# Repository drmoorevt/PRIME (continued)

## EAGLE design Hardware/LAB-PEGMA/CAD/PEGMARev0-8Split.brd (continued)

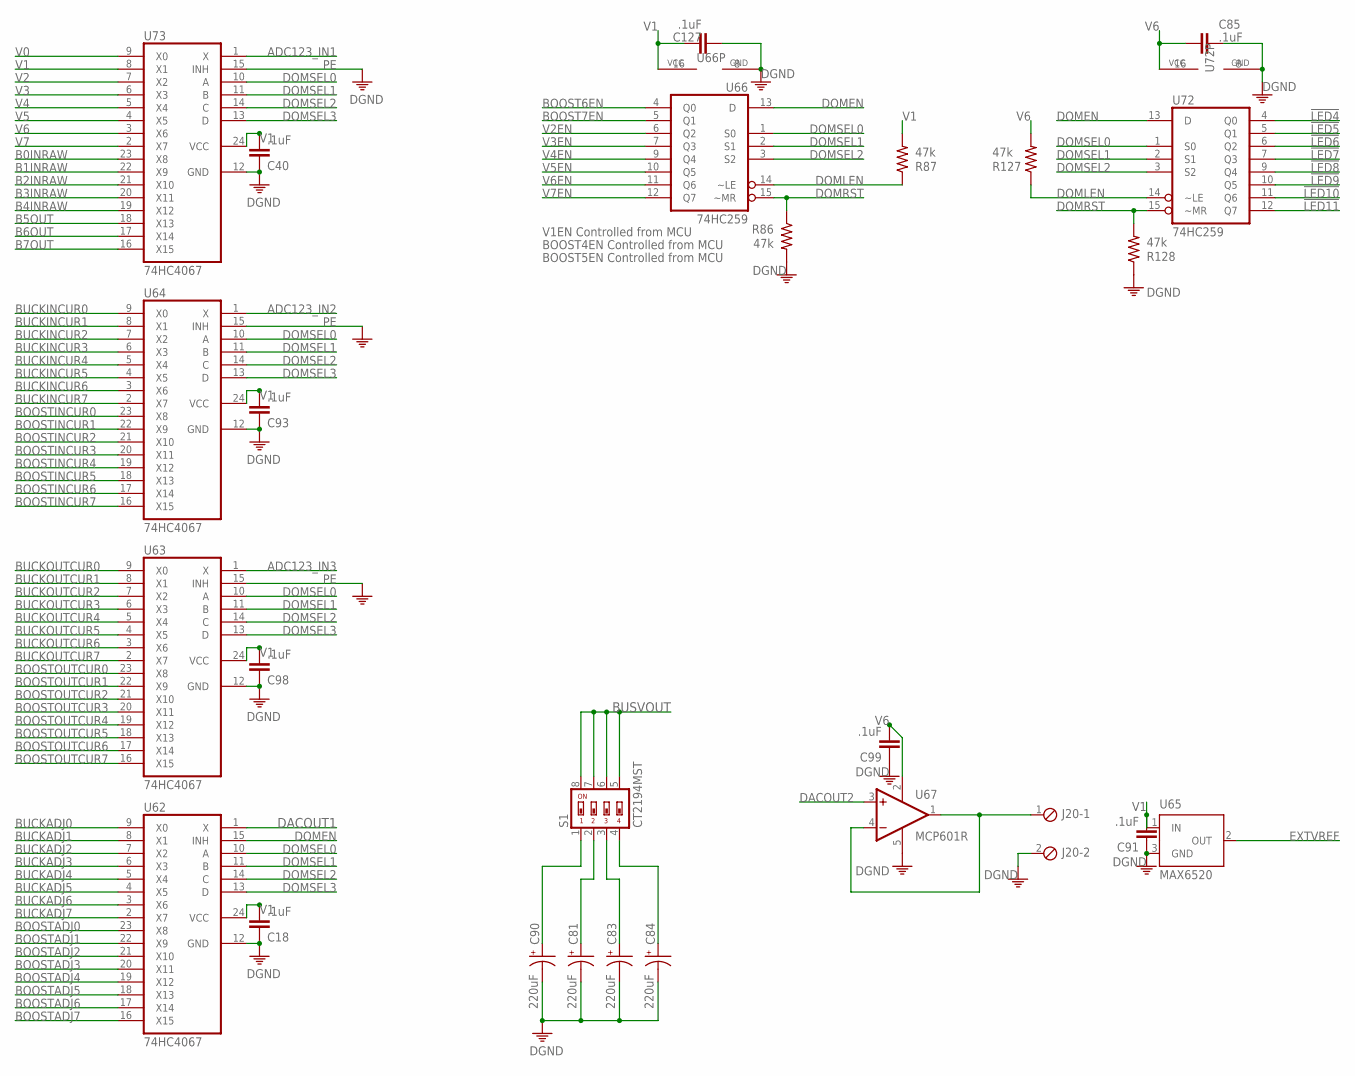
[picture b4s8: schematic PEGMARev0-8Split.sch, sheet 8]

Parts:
C18, C40, C85, C91, C93, C98, C99, C127: .1uF; C0603
C81, C83, C84, C90: 220uF; UD-8X10_NICHICON
J20: MPT2; 2POL254
R86, R87, R127, R128: 47k; R0603
S1: CT2194MST; SMS-004
U62, U63, U64, U73: 74HC4067; SO24W
U65: MAX6520; SOT23
U66, U72: 74HC259; SO16
U67: MCP601R; SOT23-5

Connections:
!LED4: U72.4 (Q0); also elsewhere on the board
!LED5: U72.5 (Q1); also elsewhere on the board
!LED6: U72.6 (Q2); also elsewhere on the board
!LED7: U72.7 (Q3); also elsewhere on the board
!LED8: U72.9 (Q4); also elsewhere on the board
!LED9: U72.10 (Q5); also elsewhere on the board
!LED10: U72.11 (Q6); also elsewhere on the board
!LED11: U72.12 (Q7); also elsewhere on the board
ADC123_IN1: U73.1 (X); also elsewhere on the board
ADC123_IN2: U64.1 (X); also elsewhere on the board
ADC123_IN3: U63.1 (X); also elsewhere on the board
B0INRAW: U73.23 (X8); also elsewhere on the board
B1INRAW: U73.22 (X9); also elsewhere on the board
B2INRAW: U73.21 (X10); also elsewhere on the board
B3INRAW: U73.20 (X11); also elsewhere on the board
B4INRAW: U73.19 (X12); also elsewhere on the board
B5OUT: U73.18 (X13); also elsewhere on the board
B6OUT: U73.17 (X14); also elsewhere on the board
B7OUT: U73.16 (X15); also elsewhere on the board
BOOST6EN: U66.4 (Q0); also elsewhere on the board
BOOST7EN: U66.5 (Q1); also elsewhere on the board
BOOSTADJ0: U62.23 (X8); also elsewhere on the board
BOOSTADJ1: U62.22 (X9); also elsewhere on the board
BOOSTADJ2: U62.21 (X10); also elsewhere on the board
BOOSTADJ3: U62.20 (X11); also elsewhere on the board
BOOSTADJ4: U62.19 (X12); also elsewhere on the board
BOOSTADJ5: U62.18 (X13); also elsewhere on the board
BOOSTADJ6: U62.17 (X14); also elsewhere on the board
BOOSTADJ7: U62.16 (X15); also elsewhere on the board
BOOSTINCUR0: U64.23 (X8); also elsewhere on the board
BOOSTINCUR1: U64.22 (X9); also elsewhere on the board
BOOSTINCUR2: U64.21 (X10); also elsewhere on the board
BOOSTINCUR3: U64.20 (X11); also elsewhere on the board
BOOSTINCUR4: U64.19 (X12); also elsewhere on the board
BOOSTINCUR5: U64.18 (X13); also elsewhere on the board
BOOSTINCUR6: U64.17 (X14); also elsewhere on the board
BOOSTINCUR7: U64.16 (X15); also elsewhere on the board
BOOSTOUTCUR0: U63.23 (X8); also elsewhere on the board
BOOSTOUTCUR1: U63.22 (X9); also elsewhere on the board
BOOSTOUTCUR2: U63.21 (X10); also elsewhere on the board
BOOSTOUTCUR3: U63.20 (X11); also elsewhere on the board
BOOSTOUTCUR4: U63.19 (X12); also elsewhere on the board
BOOSTOUTCUR5: U63.18 (X13); also elsewhere on the board
BOOSTOUTCUR6: U63.17 (X14); also elsewhere on the board
BOOSTOUTCUR7: U63.16 (X15); also elsewhere on the board
BUCKADJ0: U62.9 (X0); also elsewhere on the board
BUCKADJ1: U62.8 (X1); also elsewhere on the board
BUCKADJ2: U62.7 (X2); also elsewhere on the board
BUCKADJ3: U62.6 (X3); also elsewhere on the board
BUCKADJ4: U62.5 (X4); also elsewhere on the board
BUCKADJ5: U62.4 (X5); also elsewhere on the board
BUCKADJ6: U62.3 (X6); also elsewhere on the board
BUCKADJ7: U62.2 (X7); also elsewhere on the board
BUCKINCUR0: U64.9 (X0); also elsewhere on the board
BUCKINCUR1: U64.8 (X1); also elsewhere on the board
BUCKINCUR2: U64.7 (X2); also elsewhere on the board
BUCKINCUR3: U64.6 (X3); also elsewhere on the board
BUCKINCUR4: U64.5 (X4); also elsewhere on the board
BUCKINCUR5: U64.4 (X5); also elsewhere on the board
BUCKINCUR6: U64.3 (X6); also elsewhere on the board
BUCKINCUR7: U64.2 (X7); also elsewhere on the board
BUCKOUTCUR0: U63.9 (X0); also elsewhere on the board
BUCKOUTCUR1: U63.8 (X1); also elsewhere on the board
BUCKOUTCUR2: U63.7 (X2); also elsewhere on the board
BUCKOUTCUR3: U63.6 (X3); also elsewhere on the board
BUCKOUTCUR4: U63.5 (X4); also elsewhere on the board
BUCKOUTCUR5: U63.4 (X5); also elsewhere on the board
BUCKOUTCUR6: U63.3 (X6); also elsewhere on the board
BUCKOUTCUR7: U63.2 (X7); also elsewhere on the board
BUSVOUT: S1.5, S1.6, S1.7, S1.8; also elsewhere on the board
DACOUT1: U62.1 (X); also elsewhere on the board
DACOUT2: U67.3 (+IN); also elsewhere on the board
DOMEN: U62.15 (INH), U66.13 (D), U72.13 (D); also elsewhere on the board
DOMLEN: R87.1, R127.1, U66.14 (~LE), U72.14 (~LE); also elsewhere on the board
DOMRST: R86.1, R128.2, U66.15 (~MR), U72.15 (~MR); also elsewhere on the board
DOMSEL0: U62.10 (A), U63.10 (A), U64.10 (A), U66.1 (S0), U72.1 (S0), U73.10 (A); also elsewhere on the board
DOMSEL1: U62.11 (B), U63.11 (B), U64.11 (B), U66.2 (S1), U72.2 (S1), U73.11 (B); also elsewhere on the board
DOMSEL2: U62.14 (C), U63.14 (C), U64.14 (C), U66.3 (S2), U72.3 (S2), U73.14 (C); also elsewhere on the board
DOMSEL3: U62.13 (D), U63.13 (D), U64.13 (D), U73.13 (D); also elsewhere on the board
EXTVREF: U65.2 (OUT); also elsewhere on the board
unnamed: C83.+, S1.3
unnamed: C90.+, S1.1
unnamed: C81.+, S1.2
unnamed: C84.+, S1.4
unnamed: J20.1, U67.1 (OUT), U67.4 (-IN)
PE: C18.1, C40.1, C81.-, C83.-, C84.-, C85.1, C90.-, C91.1, C93.1, C98.1, C99.1, C127.1, J20.2, R86.2, R128.1, U62.12 (GND), U63.12 (GND), U63.15 (INH), U64.12 (GND), U64.15 (INH), U65.3 (GND), U66.8 (GND), U67.5 (V-), U72.8 (GND), U73.12 (GND), U73.15 (INH); also elsewhere on the board
V0: U73.9 (X0); also elsewhere on the board
V1: C18.2, C40.2, C91.2, C93.2, C98.2, C127.2, R87.2, U62.24 (VCC), U63.24 (VCC), U64.24 (VCC), U65.1 (IN), U66.16 (VCC), U73.8 (X1), U73.24 (VCC); also elsewhere on the board
V2: U73.7 (X2); also elsewhere on the board
V2EN: U66.6 (Q2); also elsewhere on the board
V3: U73.6 (X3); also elsewhere on the board
V3EN: U66.7 (Q3); also elsewhere on the board
V4: U73.5 (X4); also elsewhere on the board
V4EN: U66.9 (Q4); also elsewhere on the board
V5: U73.4 (X5); also elsewhere on the board
V5EN: U66.10 (Q5); also elsewhere on the board
V6: C85.2, C99.2, R127.2, U67.2 (V+), U72.16 (VCC), U73.3 (X6); also elsewhere on the board
V6EN: U66.11 (Q6); also elsewhere on the board
V7: U73.2 (X7); also elsewhere on the board
V7EN: U66.12 (Q7); also elsewhere on the board

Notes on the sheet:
V1EN Controlled from MCU
BOOST4EN Controlled from MCU
BOOST5EN Controlled from MCU

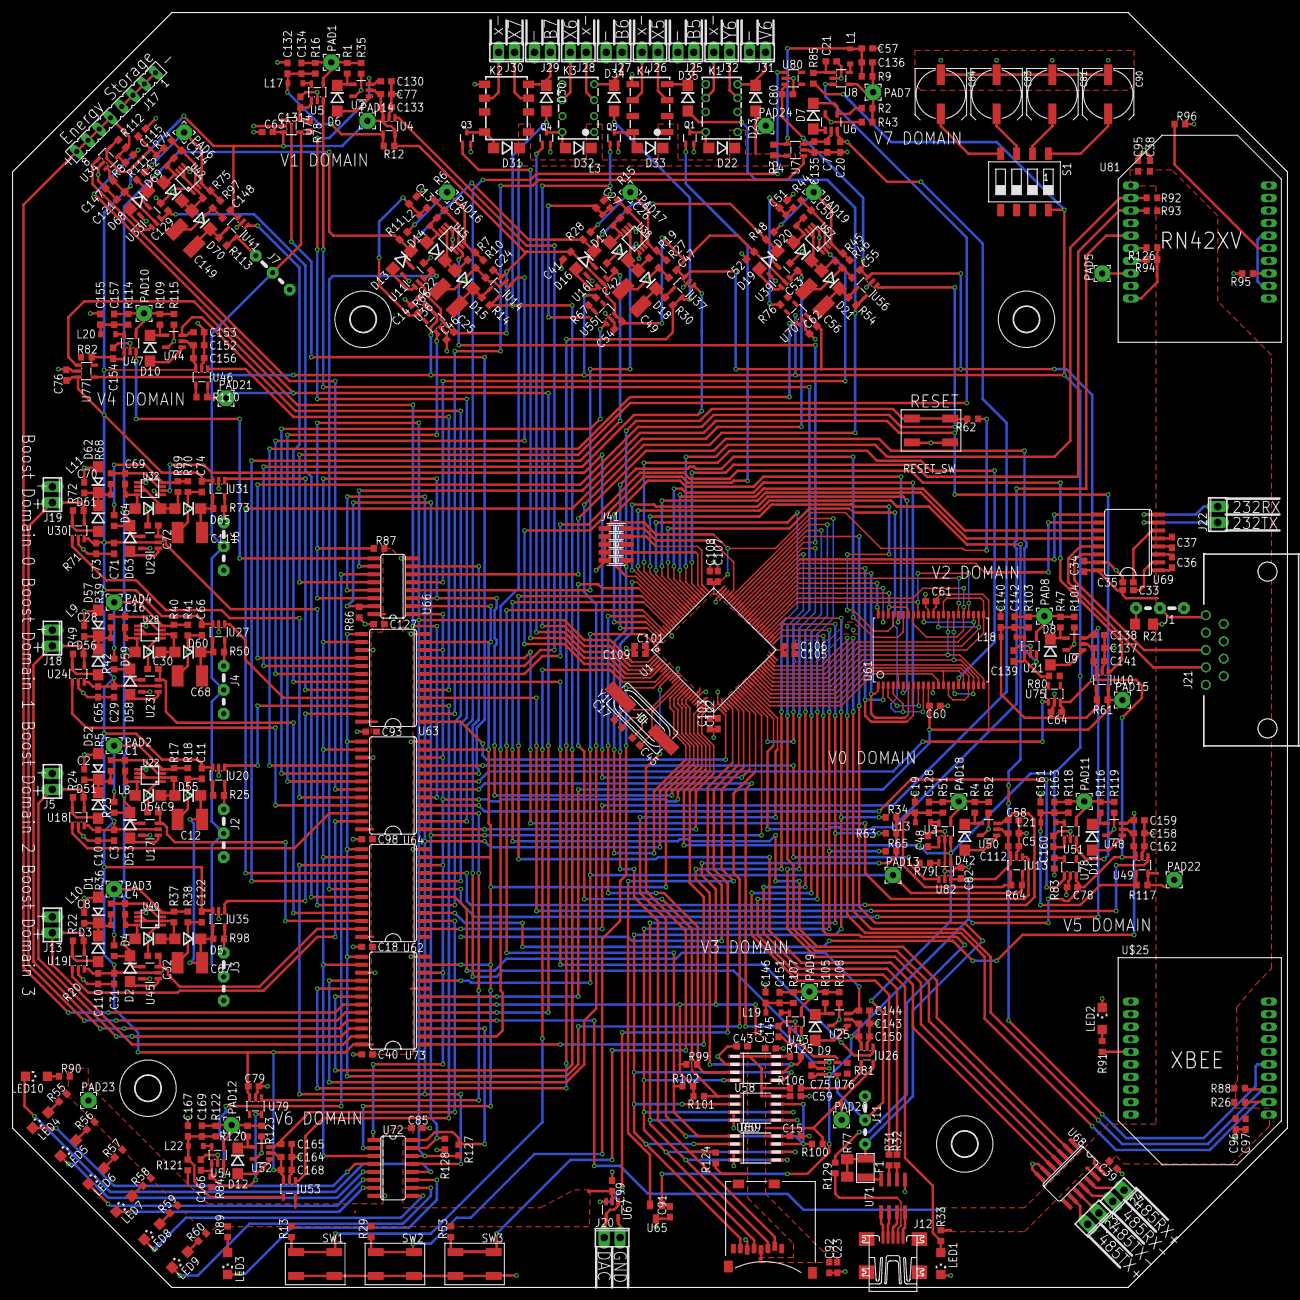
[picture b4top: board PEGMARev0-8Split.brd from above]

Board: 2 copper layers, 203.2 x 203.2 mm, 508 parts (0 on the bottom side), 341 nets.

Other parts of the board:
U$1, U$2, U$3, U$4: 4,1

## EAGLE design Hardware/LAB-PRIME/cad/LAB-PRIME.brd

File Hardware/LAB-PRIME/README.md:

LAB-PRIME
=========
* This folder contains the technical data for the LAB-PRIME (Precise Real-Time In-Circuit Micro EMS)

cad:  Contains the files and libraries for the schematic and circuit board 
docs: Contains product specification, BOM, datasheets, documentation
revs: Contains board revisions that have gone to manufacture

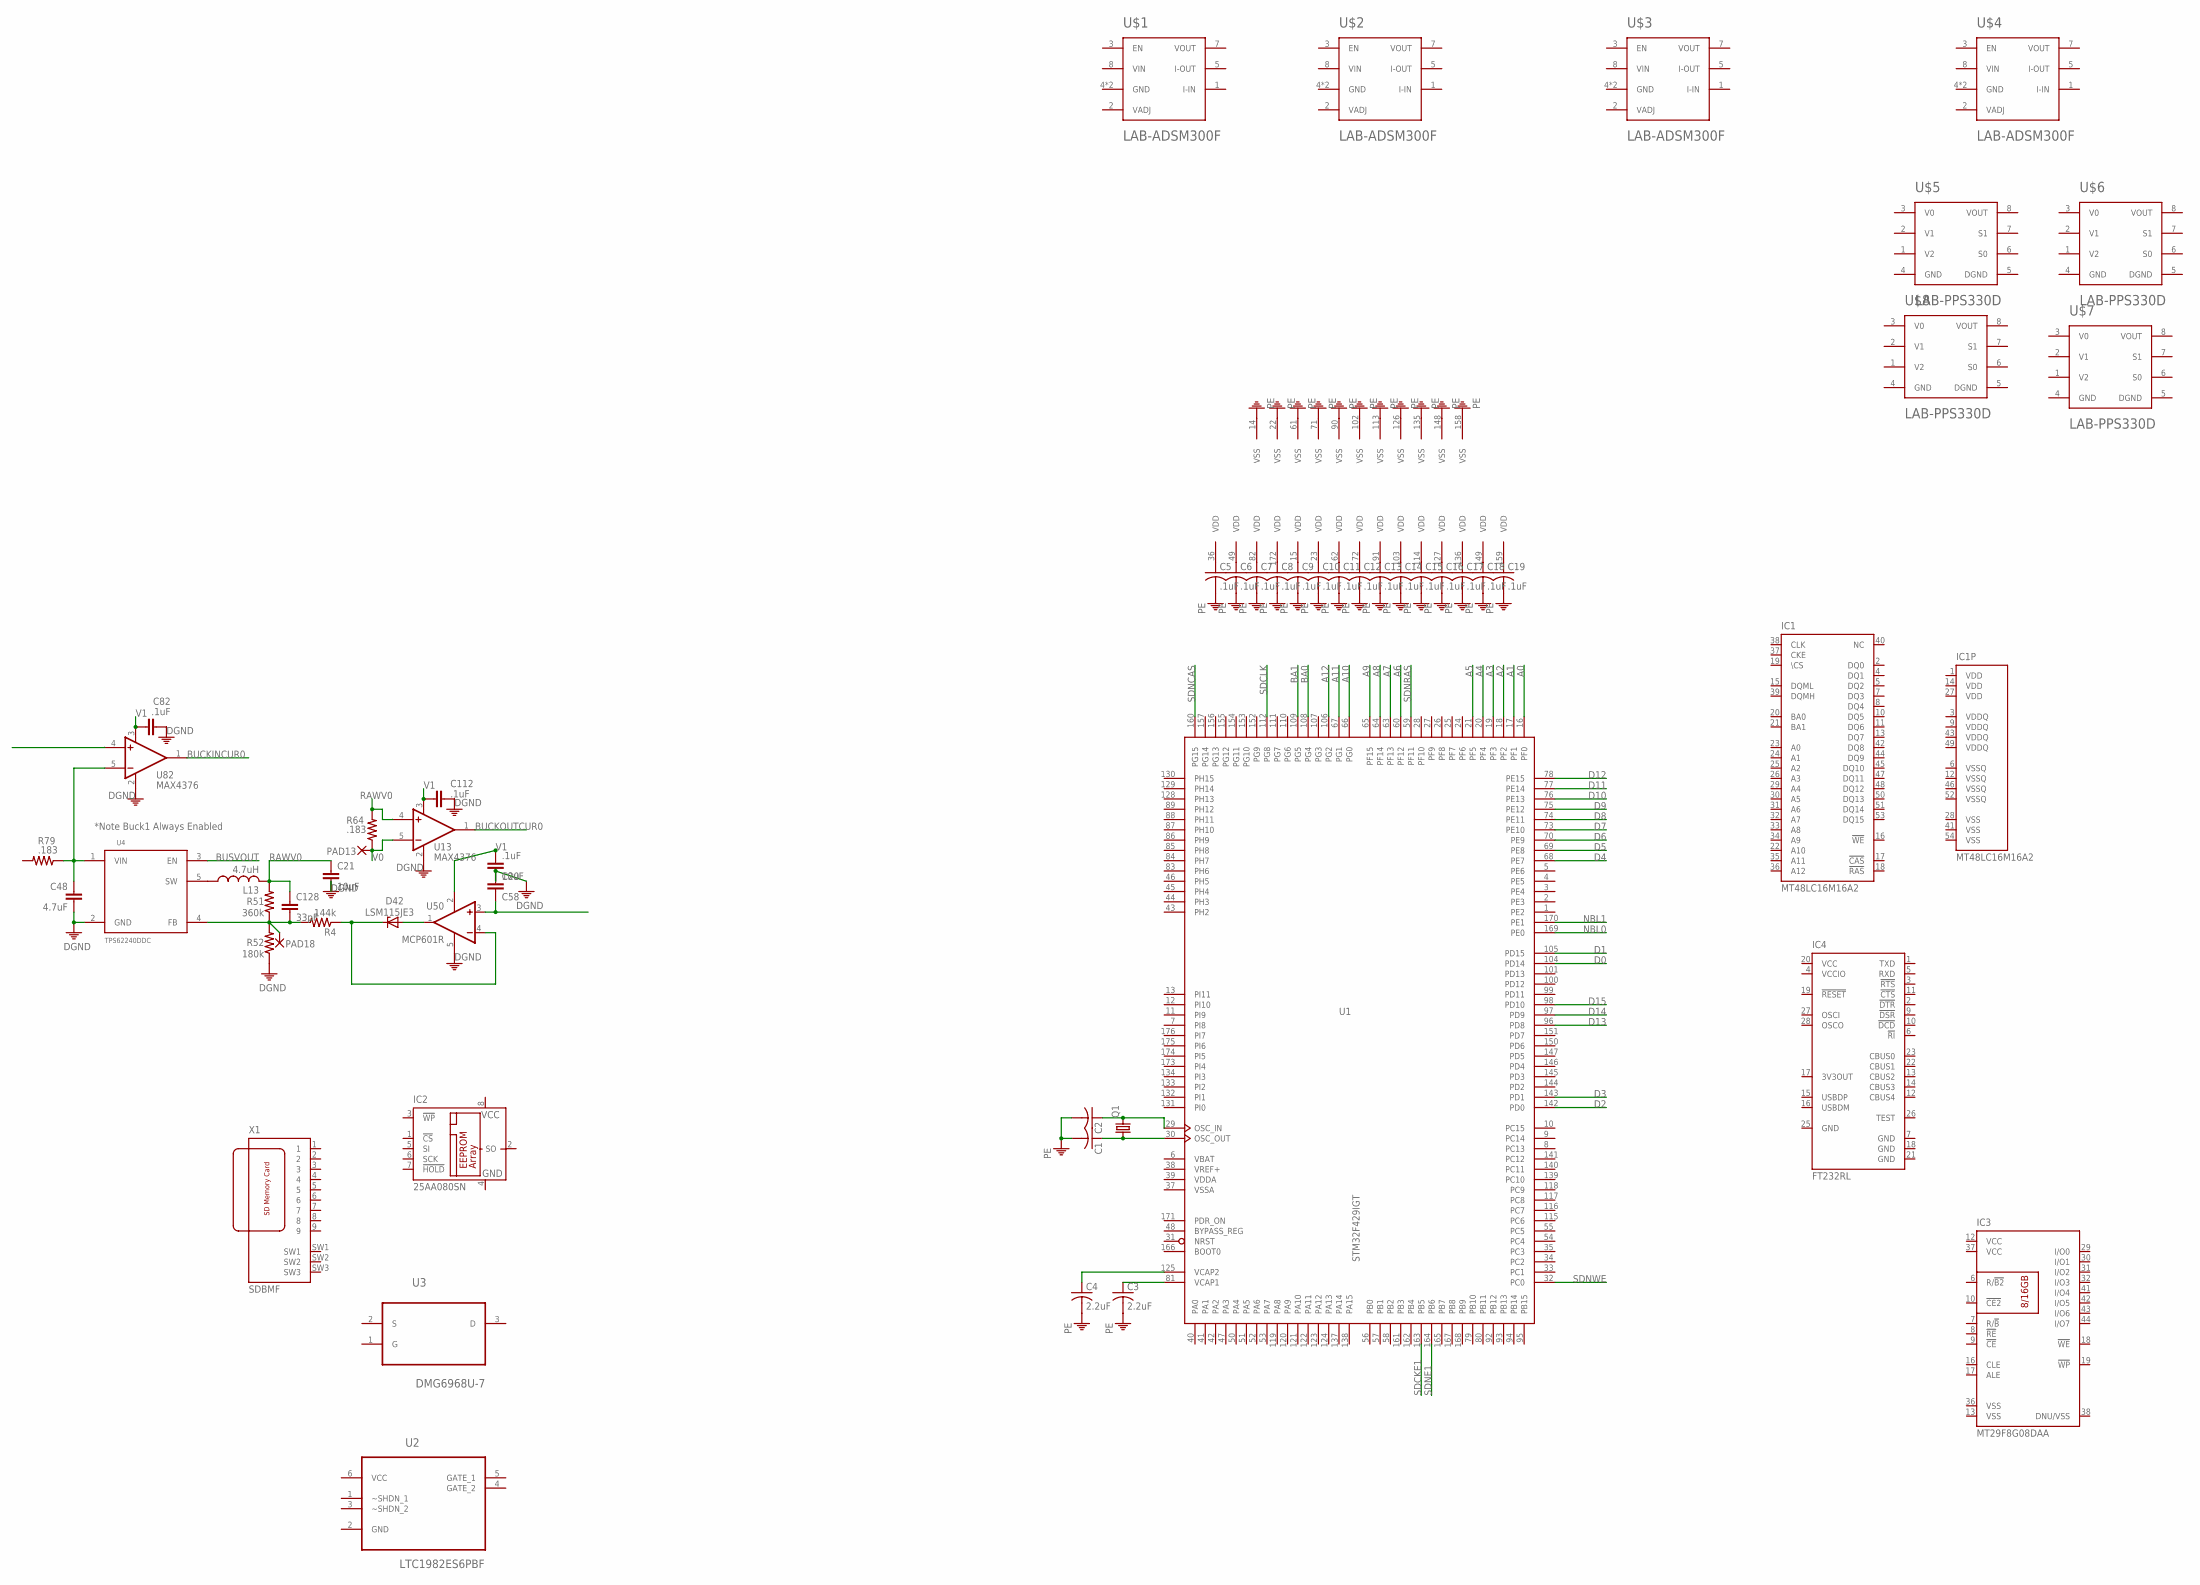
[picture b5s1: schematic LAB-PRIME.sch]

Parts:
C1, C2: C-USC0402K; C0402K
C3, C4: 2.2uF; C0402K
C5, C6, C7, C8, C9, C10, C11, C12, C13, C14, C15, C16, C17, C18, C19: .1uF; C0402K
C20, C82, C112: .1uF; C0603
C21, C58: 10uF; C0603
C48: 4.7uF; C0603
C128: 33pF; C0603
D42: LSM115JE3; DO214BA
IC1: MT48LC16M16A2; TSOP54-400
IC2: 25AA080SN; SO-08
IC3: MT29F8G08DAA; TSOP48
IC4: FT232RL; SSOP28
L13: 4.7uH; L1008/2520METRIC
PAD13, PAD18: 2,54/1,0
Q1: CRYSTALCTS406; CTS406
R4: 144k; R0603
R51: 360k; R0603
R52: 180k; R0603
R64, R79: .183; R0603
U1: STM32F429IGT; LQFP176
U2: LTC1982ES6PBF; SOT95P280X145-6N
U3: DMG6968U-7; SOT95P240X110-3N
U4: TPS62240DDC; SOT23-5
U13, U82: MAX4376; SOT23-5
U50: MCP601R; SOT23-5
U$1, U$2, U$3, U$4: LAB-ADSM300F; LAB-ASDM300F
U$5, U$6, U$7, U$8: LAB-PPS330D
X1: SDBMF; SDBMF-009XXBXX2

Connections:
A0: U1.16 (PF0)
A1: U1.17 (PF1)
A2: U1.18 (PF2)
A3: U1.19 (PF3)
A4: U1.20 (PF4)
A5: U1.21 (PF5)
A6: U1.60 (PF12)
A7: U1.63 (PF13)
A8: U1.64 (PF14)
A9: U1.65 (PF15)
A10: U1.66 (PG0)
A11: U1.67 (PG1)
A12: U1.106 (PG2)
BA0: U1.108 (PG4)
BA1: U1.109 (PG5)
BUCKADJ0: C58.1, U50.3 (+IN)
BUCKINCUR0: U82.1 (OUT)
BUCKOUTCUR0: U13.1 (OUT)
BUSVOUT: U4.3 (EN), U82.4 (+IN)
D0: U1.104 (PD14)
D1: U1.105 (PD15)
D2: U1.142 (PD0)
D3: U1.143 (PD1)
D4: U1.68 (PE7)
D5: U1.69 (PE8)
D6: U1.70 (PE9)
D7: U1.73 (PE10)
D8: U1.74 (PE11)
D9: U1.75 (PE12)
D10: U1.76 (PE13)
D11: U1.77 (PE14)
D12: U1.78 (PE15)
D13: U1.96 (PD8)
D14: U1.97 (PD9)
D15: U1.98 (PD10)
G: U3.1 (G)
GND: IC2.4 (GND), IC4.7 (GND), IC4.18 (GND), IC4.21 (GND), IC4.25 (GND), U$1.4 (GND), U$1.6 (GND), U$2.4 (GND), U$2.6 (GND), U$3.4 (GND), U$3.6 (GND), U$4.4 (GND), U$4.6 (GND), U$5.4 (GND), U$6.4 (GND), U$7.4 (GND), U$8.4 (GND)
unnamed: C1.1, Q1.1, U1.30 (OSC_OUT)
unnamed: C2.1, Q1.3 (2), U1.29 (OSC_IN)
unnamed: C4.1, U1.125 (VCAP2)
unnamed: C3.1, U1.81 (VCAP1)
unnamed: C5.1, U1.36 (VDD)
unnamed: C6.1, U1.49 (VDD)
unnamed: C7.1, U1.82 (VDD)
unnamed: C8.1, U1.172 (VDD)
unnamed: C9.1, U1.15 (VDD)
unnamed: C10.1, U1.23 (VDD)
unnamed: C11.1, U1.62 (VDD)
unnamed: C12.1, U1.72 (VDD)
unnamed: C13.1, U1.91 (VDD)
unnamed: C14.1, U1.103 (VDD)
unnamed: C15.1, U1.114 (VDD)
unnamed: C16.1, U1.127 (VDD)
unnamed: C17.1, U1.136 (VDD)
unnamed: C18.1, U1.149 (VDD)
unnamed: C19.1, U1.159 (VDD)
unnamed: D42.C, R4.1, U50.4 (-IN)
unnamed: L13.1, U4.5 (SW)
unnamed: C48.1, R79.1, U4.1 (VIN), U82.5 (-IN)
unnamed: C128.2, PAD18.1, R4.2, R51.1, R52.2, U4.4 (FB)
unnamed: D42.A, U50.1 (OUT)
NBL0: U1.169 (PE0)
NBL1: U1.170 (PE1)
PE: C1.2, C2.2, C3.2, C4.2, C5.2, C6.2, C7.2, C8.2, C9.2, C10.2, C11.2, C12.2, C13.2, C14.2, C15.2, C16.2, C17.2, C18.2, C19.2, C20.1, C21.2, C48.2, C58.2, C82.1, C112.1, R52.1, U1.14 (VSS), U1.22 (VSS), U1.61 (VSS), U1.71 (VSS), U1.90 (VSS), U1.102 (VSS), U1.113 (VSS), U1.126 (VSS), U1.135 (VSS), U1.148 (VSS), U1.158 (VSS), U4.2 (GND), U13.2 (V-), U50.5 (V-), U82.2 (V-)
RAWV0: C21.1, C128.1, L13.2, R51.2, R64.2, U13.4 (+IN)
SDCKE1: U1.163 (PB5)
SDCLK: U1.112 (PG8)
SDNCAS: U1.160 (PG15)
SDNE1: U1.164 (PB6)
SDNRAS: U1.59 (PF11)
SDNWE: U1.32 (PC0)
V0: PAD13.1, R64.1, U13.5 (-IN), U$5.3 (V0), U$6.3 (V0), U$7.3 (V0), U$8.3 (V0)
V1: C20.2, C82.2, C112.2, U13.3 (V+), U50.2 (V+), U82.3 (V+)
VBAT: U1.6 (VBAT)
VCC: IC2.8 (VCC), IC3.12 (VCC), IC3.37 (VCC), IC4.20 (VCC), U2.6 (VCC)
VCCIO: IC4.4 (VCCIO)
VDD: IC1.1 (VDD), IC1.14 (VDD), IC1.27 (VDD)
VDDA: U1.39 (VDDA)
VDDQ: IC1.3 (VDDQ), IC1.9 (VDDQ), IC1.43 (VDDQ), IC1.49 (VDDQ)
VIN: U$1.8 (VIN), U$2.8 (VIN), U$3.8 (VIN), U$4.8 (VIN)
VREF+: U1.38 (VREF+)
VSS: IC1.28 (VSS), IC1.41 (VSS), IC1.54 (VSS), IC3.13 (VSS), IC3.36 (VSS)
VSSA: U1.37 (VSSA)
VSSQ: IC1.6 (VSSQ), IC1.12 (VSSQ), IC1.46 (VSSQ), IC1.52 (VSSQ)

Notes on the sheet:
*Note Buck1 Always Enabled

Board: 2 copper layers, 56 parts (1 on the bottom side), 37 nets, no tracks yet.

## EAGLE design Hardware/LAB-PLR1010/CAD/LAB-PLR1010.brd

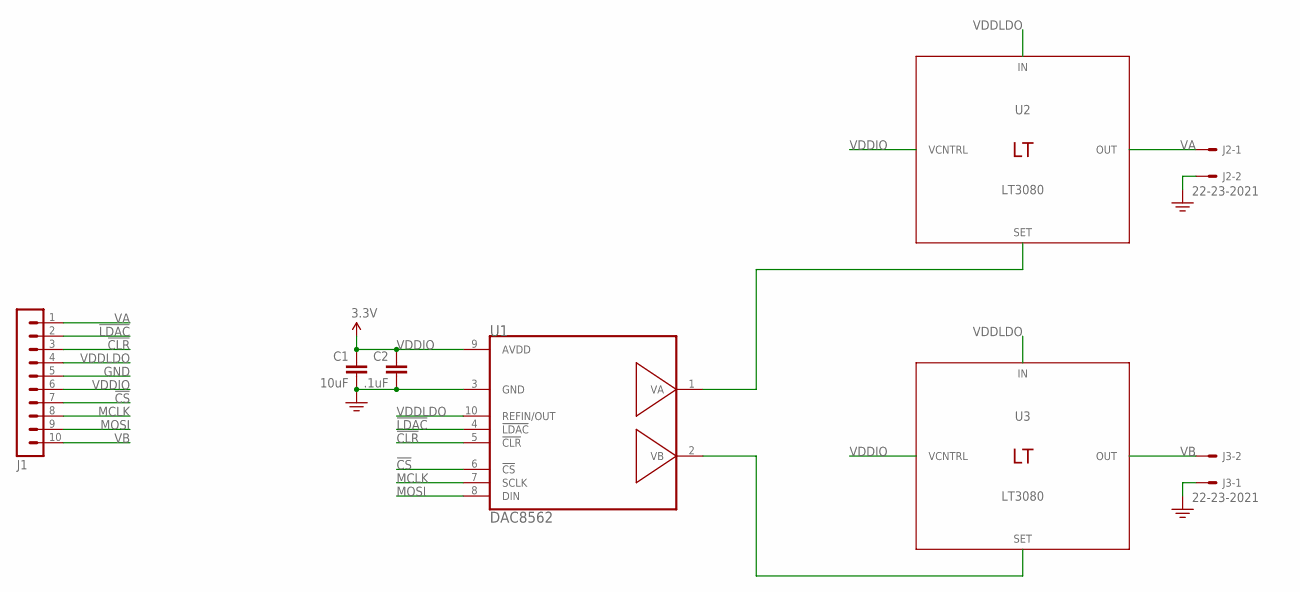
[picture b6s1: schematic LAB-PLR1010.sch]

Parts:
C1: 10uF; 0603-CAP
C2: .1uF; 0603-CAP
J1: MA10-1W
J2, J3: 22-23-2021
U1: DAC8562; MSOP10
U2, U3: LT3080; DDPAK5(Q)

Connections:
!CLR: J1.3, U1.5 (!CLR)
!CS: J1.7, U1.6 (!CS)
!LDAC: J1.2, U1.4 (!LDAC)
GND: C1.2, C2.2, J1.5, J2.2, J3.1, U1.3 (GND)
MCLK: J1.8, U1.7 (SCLK)
MOSI: J1.9, U1.8 (DIN)
unnamed: U1.1 (VA), U2.2 (SET)
unnamed: U1.2 (VB), U3.2 (SET)
VA: J1.1, J2.1, U2.3 (OUT), U2.TAB (OUT)
VB: J1.10, J3.2, U3.3 (OUT), U3.TAB (OUT)
VDDIO: C1.1, C2.1, J1.6, U1.9 (AVDD), U2.4 (VCNTRL), U3.4 (VCNTRL)
VDDLDO: J1.4, U1.10 (REFIN/OUT), U2.5 (IN), U3.5 (IN)

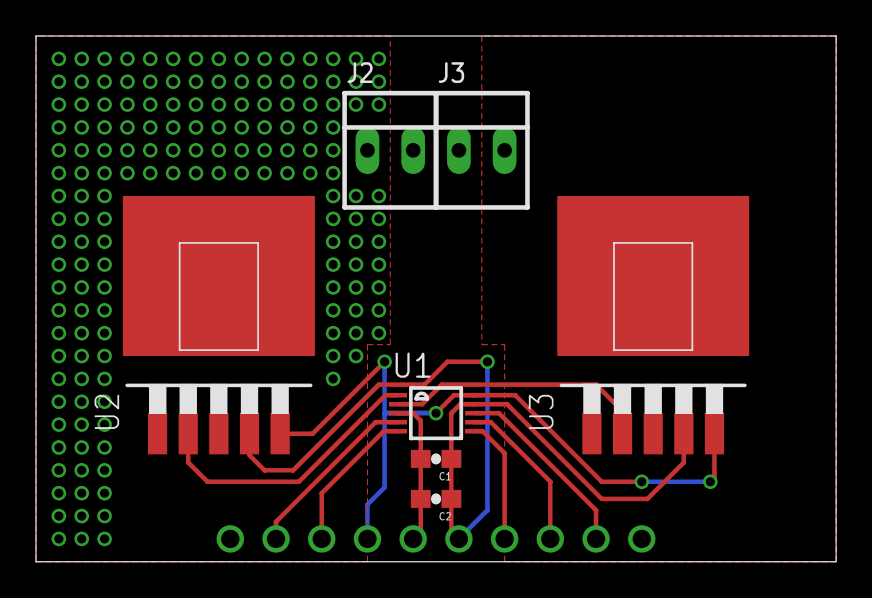
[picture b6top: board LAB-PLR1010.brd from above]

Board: 2 copper layers, 44.5 x 29.2 mm, 8 parts (1 on the bottom side), 12 nets.

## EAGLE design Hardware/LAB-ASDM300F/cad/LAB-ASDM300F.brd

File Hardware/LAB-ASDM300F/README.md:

LAB-ASDM300F
=========
* This folder contains the technical data for the LAB-ASDM300F (Adjustable Step Down Module, 300mA with feedback). 

cad:  Contains the files and libraries for the schematic and circuit board 
docs: Contains product specification, BOM, datasheets, documentation
revs: Contains board revisions that have gone to manufacture

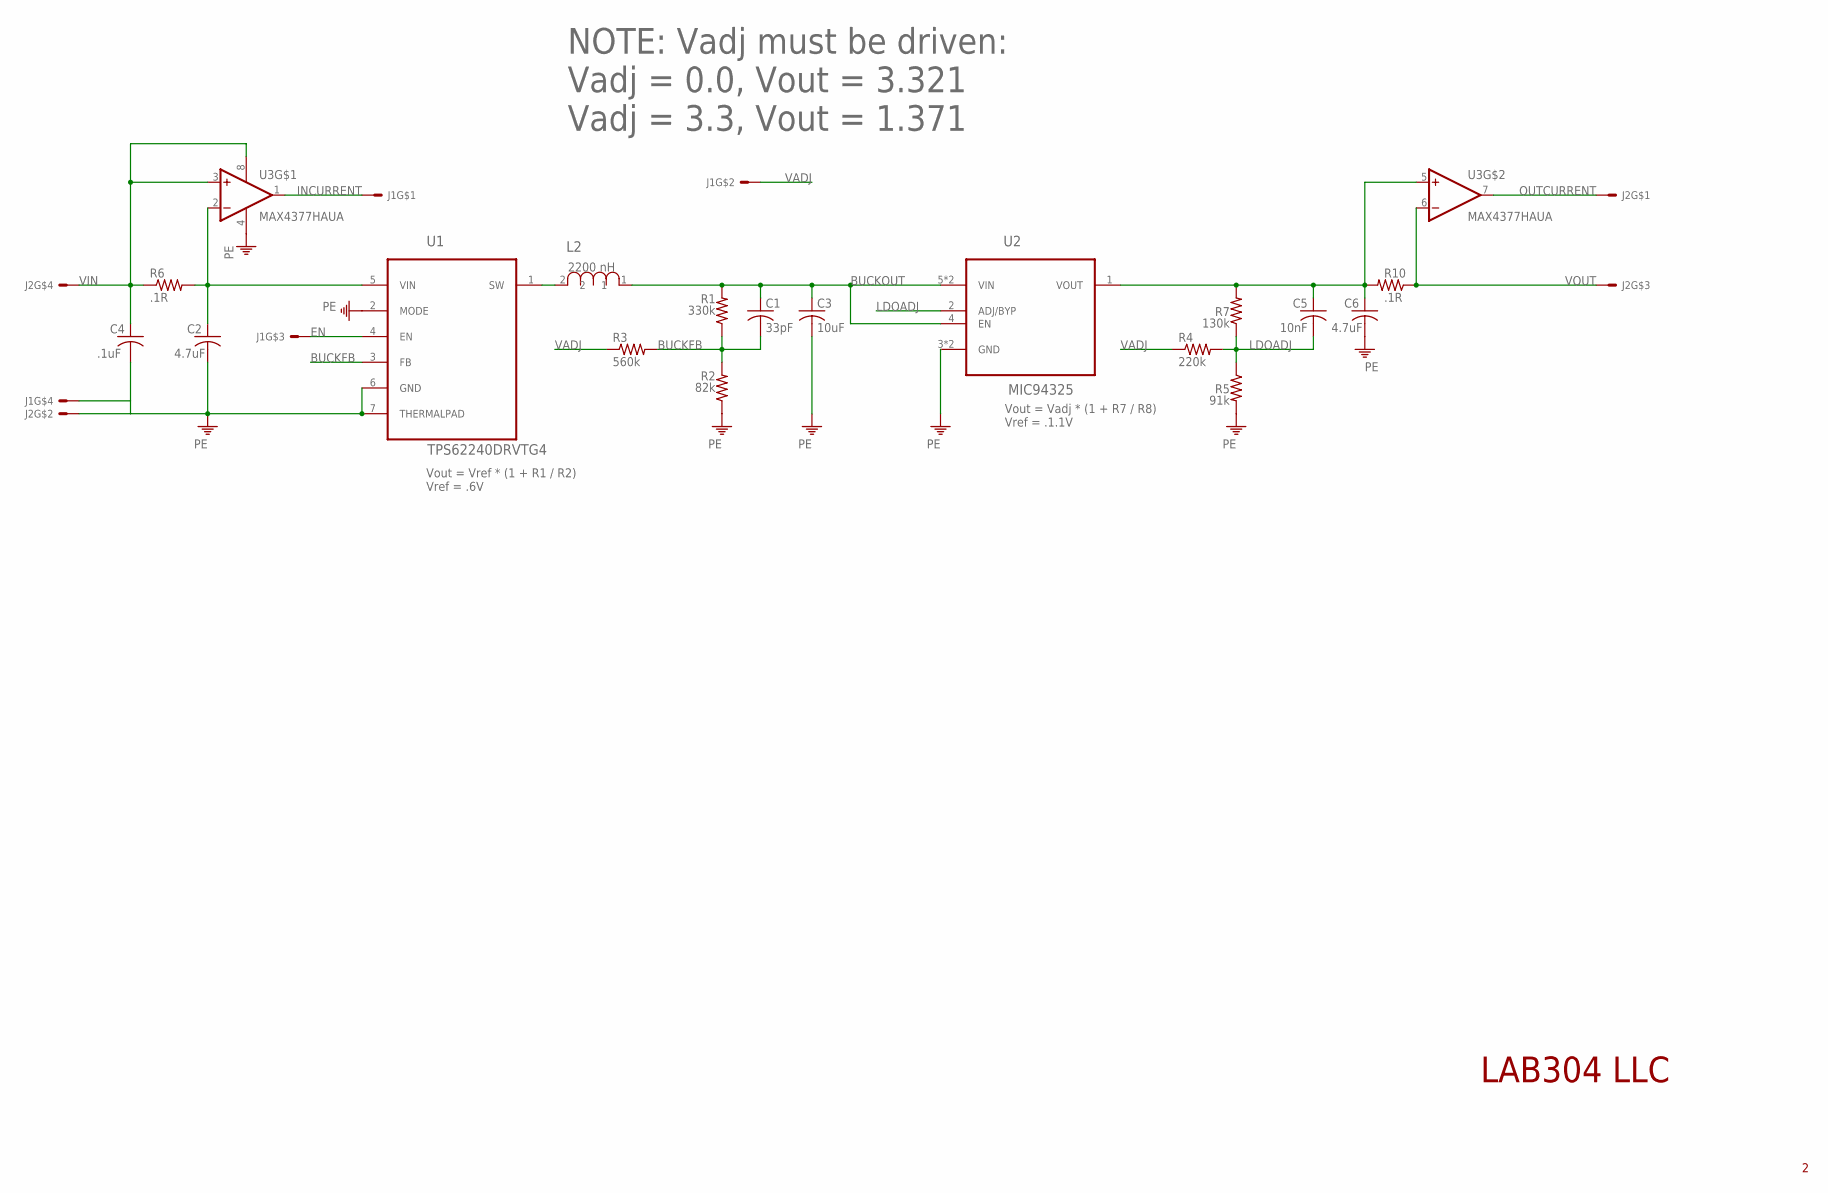
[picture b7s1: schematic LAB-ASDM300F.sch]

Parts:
C1: 33pF; C0603
C2, C6: 4.7uF; C0603
C3: 10uF; C0603
C4: .1uF; C0603
C5: 10nF; C0603
J1, J2: SULLINSSMTHEADER-4; SMTHEADER-4
L2: 2200 nH; INDC2520X18N
R1: 330k; R0603
R2: 82k; R0603
R3: 560k; R0603
R4: 220k; R0603
R5: 91k; R0603
R6, R10: .1R; R0603
R7: 130k; R0603
U1: TPS62240DRVTG4; SON65P210X210X80-7N
U2: MIC94325; SON65P160X160X80-7N
U3: MAX4377HAUA; UMAX8

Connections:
BUCKFB: C1.2, R1.1, R2.2, R3.2, U1.3 (FB)
BUCKOUT: C1.1, C3.1, L2.1, R1.2, U2.4 (EN), U2.5 (VIN), U2.6 (VIN)
EN: J1.P$3, U1.4 (EN)
INCURRENT: J1.P$1, U3.1 (OUT)
LDOADJ: C5.2, R4.2, R5.1, R7.1, U2.2 (ADJ/BYP)
unnamed: L2.2, U1.1 (SW)
unnamed: C2.1, R6.2, U1.5 (VIN), U3.2 (-IN)
unnamed: C5.1, C6.1, R7.2, R10.2, U2.1 (VOUT), U3.5 (+IN)
OUTCURRENT: J2.P$1, U3.7 (OUT)
PE: C2.2, C3.2, C4.2, C6.2, J1.P$4, J2.P$2, R2.1, R5.2, U1.2 (MODE), U1.6 (GND), U1.7 (THERMALPAD), U2.3 (GND), U2.7 (GND), U3.4 (V-)
VADJ: J1.P$2, R3.1, R4.1
VIN: C4.1, J2.P$4, R6.1, U3.3 (+IN), U3.8 (V+)
VOUT: J2.P$3, R10.1, U3.6 (-IN)

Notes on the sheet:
Vout = Vref * (1 + R1 / R2) Vref = .6V
Vout = Vadj * (1 + R7 / R8) Vref = .1.1V
NOTE: Vadj must be driven: Vadj = 0.0, Vout = 3.321 Vadj = 3.3, Vout = 1.371
LAB304 LLC

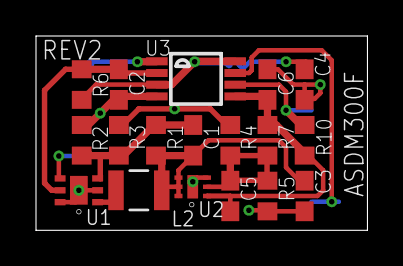
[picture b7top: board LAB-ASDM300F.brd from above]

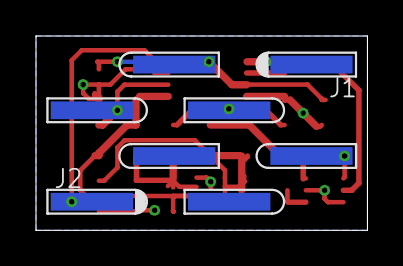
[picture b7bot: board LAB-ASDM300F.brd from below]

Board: 2 copper layers, 18.4 x 10.8 mm, 20 parts (2 on the bottom side), 13 nets.

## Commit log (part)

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2013-08-21 adding ignore
2013-08-21 Adding datasheets and beginning generic refactor
2013-08-25 added an unexpected rx callback to AppCommConfig -- no need to throw away the byte, the app might have use for it
    added configurations for all UARTS
    consolidated pin configurations using inspiration from the stdLib
    next up is the analog module -- ultimately trying to get to a point where I dont have to call GPIO_init in order to get tests to run
2013-08-25 Adding core libraries to VCS
2013-08-26 New directory structure will contain all development work (HW,FW,SW,Docs)
    Adding the STM32 StdLib for reference when creating device drivers
2013-08-28 Tests can now be called from and supply data to matlab -- still working on the protocol
    Tests_run now controls the comm port and listens for incoming test requests and supplies the results.
    Next I need to figure out what is wrong with EEPROM -- it was working 2 weeks ago, but the readback is failing now. Likely culprit is GPIO_init -- need to write pin and clock inits for spi and EEPROM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
2013-09-02 Adding PEM300 initial work
    Adding TestConsole.m -- This will be the interface to the PEGMA board
    Worked on the protocol between MATLAB and DUT -- Fixture can now respond with a variable number of bytes and channels.
    Added CRC utils to both fixture and DUT, but they are not implemented as part of the protocol yet
2014-01-15 Completed LAB-PEM300 Design, Layout, BOM
2014-01-30 Hierarchy changes and renamed PEM300 to ICM100 (interposing current monitor)
2014-01-31 Adding in module for SDCard -- stubbing from SerialFlash which will be used when the parts arrive
2014-02-23 Added support for the serialflash chip
2014-04-06 Structural work on the analog section. Not fully implemented yet, but will eventually transition to a continuous measure / control loop. Added stubs (needs adjustment) for the LP/XLP write function f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
2014-04-25 Voltage sweep test now working EEPROM now adjusting voltage according to state working on the SerialFlash to do the same thing... voltage doesnt wanna drop very low for some reason
2014-05-14 1) Added power profile functionality to EEPROM.c 2) Refactored EEPROM states and profiles in the same way as SerialFlash
2014-05-20 1) Modifications to allow break up directWrite into writing pages of Serial Flash
2014-05-21 1) Completed the fine delay functionality 2) Reworked how time is handled by the time module *) Need to consider breaking apart splitting time into a time and timer module.
2014-06-03 Updates to sdcard resp codes
2014-06-10 finished with variable SPI related changes to EEPROM + tests
    now working on serialflash + tests
2014-06-16 Tests now accept variable length arguments, working on CRC functionality ... again
2014-06-17 Added output current average oAvg to tests. Added multiple test runs and a stem plot to software
2014-06-26 1) Changed tests to conform to running 1 at a time. All averaging will need to be done by the host (matlab). 2) This allows for a bigger (higher resolution) buffer (4096->8192) bytes 3) Added test ar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
2014-06-30 1) Completed variable arguments to test11 *) Need to create a test12-14 argGen and working on test11-14 result parser *) Need to use DMA for ADC conversions in order to achieve a faster than 5us conv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
2014-07-03 1) Adding support for bluetooth -- tested via PC 2) Adding support for ZigBee -- untested 3) Added EEPROM_write result return codes 4) Now using FIFOs on the ADC DMAs 5) Now disabling the SysTick dur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
2014-07-06 1) Modifications to allow tests to be automated (and reproducible) 2) Now using open drain on the SPI pins, prevents leakage into the domain and doesn't seem to have any adverse impact 3) Turned off 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
2014-07-07 Test script updates
2014-07-08 1) Now using my own testPlot file to make graphs. Seems to be more adjustable. *) Removed ploty4.m
2014-07-15 These tests are ready to roll ... finishing work on optimizing SDCard transactions
2014-07-21 Just committing to transfer work to another computer -- still working on the test11Analyzer
2014-07-22 Of course ...
2014-07-25 1) Fixing a mA -> V conversion issue because I ordered the wrong part 2) Fixing the SDCard to actually use the randomly generated address
2014-08-12 Added all references and related work nearly complete -- just need to differentiate EDPM from the referenced
2014-08-19 Result Synchronization
    Trying to get GitHub on the mac to work nicely with TortoiseGit on the
    PC
2014-08-27 Further work to the IODVS paper -- verbage and graphs.
2014-08-29 Updates to the PPT flowcharts
2014-08-29 Updates to the graphing suite + now measuring microjoules
2014-09-08 1) Test console is set up to run the slow SDCard 2048 times. 2) Added variable wait timing to SDCard test -- the SDCards appear to NEED the SPI clocks in order to function, so they have NEGATIVE (del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
2014-09-10 1) Copied new dev header from Keil to fix peripheral reset register
2014-09-16 1) Added blocklen and capacity to the sSDCard structure -- they are now SDCard dependent! 2) Fixed a problem in SDCard_writeBlock where the address was being sent in LE format -- this was totally wro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
2014-09-22 Adding official test results for IODVS paper
2014-10-03 More work on the RTAS paper
2014-10-12 Updates to the abstract and to the energy analysis spreadsheet
2014-10-16 1) Added a AppNote for the HIH6130 2) Finished flowcharts and crops
2014-10-16 Adding Kingston Results
2014-10-20 1) Updates to the RTAS paper -- now on RevF thanks to another MSWord crash... 2) Added an arrow to the Flowcharts.pptx 3) More work on EnergyAnalysis.xlsx
2014-11-19 1) Initial work on getting USB FS mode working -- adding in the peripheral example, will come out upon completion. 2) Just minor text edits to the other files
2014-11-21 1) More work getting the USB code to conform to the project
2014-11-22 1) USB VCP working at maximum speed (looks like 512Kbps for now...) 2) Committing this now because I'm about to break out the descriptor stuff into a separate config file (to clean up the usbvcp.c fi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
2014-11-25 1) Fixing some inconsistencies that were introduced by changing from an EEPROM symbol to a serial flash symbol
2014-12-03 1) First shot at implementing SRAM ... 2) Made USBVCP compilable 3) Had to change test buffer size to accommodate USB buffer 4) Added linker-function optimization which allows this to compile within 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
2014-12-06 1) Adding a POST for the SRAM 2) May have gone a little overboard with the volatile -- theres a whole mess of issues caused by turning on optimizations and (see i2cbb setup time addition). Need to go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
    *Next working on moving samples into the SRAM
2014-12-09 1) Messing around with SRAM tests
2014-12-17 1) Finished the Rev0 board layout ... but its wrong ... (feedback adjustments are messed up -- fixing now)
2014-12-22 1) Adding new pinouts -- WIP
2014-12-29 1) Finished the Rev1 BOM 2) R1 was inadvertently named 330k, changed the designator and bumped the rev. Sticking with Rev2 until new boards go out -- changes may be necessary ...
2015-01-07 1) Adjusted the silkscreen for clarity (size and location) 2) Moved the track under the LDO to be squarely underneath the resistor (now kinks before the resistor)
2015-01-09 1) Adding the LTSpice model for the new PPS330D 2) Updating shunt resistor in the ReferenceGuide.xlsx to show the actual resistor specified in the BOM
2015-01-13 1) Shaved a few mils off .. this is the ACTUAL REV1
2015-01-20 1) Removing the tDoc layer from the CAM file
2015-01-20 1) Consolidating on the PLR1010 naming convention
2015-01-20 1) Adding a README.md for the ASDM
2015-01-21 1) This commit contains a lot of work necessary to work with the esp8266 module
2015-01-23 1) Moving to the dual DAC approach ... adding the datasheet
2015-01-29 1) Layout changes to the PLR1010
2015-01-30 1) Adding connector datasheet
2015-01-31 1) Committing final Rev0 of the PLR5010
2015-02-03 1) Adding the SDRAM used on the STM32F429 discovery board
2015-02-13 1) Breaking firmware into 3 projects: *) The original PEGMA firmware *) Firmware to be developed for the STM32F429 Discovery board *) Firmware developed for the final PRIME board
2015-02-24 1) Initial ANTEPRIME commit
2015-02-25 1) Removing erroneously versioned filed
2015-02-25 1) Updated the project and removed a user-specific project file
2015-03-18 1) Working on the analog module. The ADC now continuously samples.
2015-04-01 1) Adding basic support for the PLR5010D
2015-04-21 1) Committing the PLR5010D DAC tests
2015-05-18 1) Finished first draft of introduction and ported IODVS findings.
2015-09-16 1) Adding Dissertation folder
2015-09-27 1) checkpoint
2015-10-11 1) Added PEGMA schematics. 2) Fixed minor grammar problems in intro.
2015-10-19 1) Created Appendix A, formatting.
2015-10-24 1) Cleaning up the file system a bit.
2015-10-26 1) Finishing up Chapter2 ... needs a quick review.
2015-10-29 1) Fixed all error references in chapter 3
2015-11-05 1) Adding comments from Dr. Deans review
2015-11-12 1) Committing Dr. Deans comments on Ch3
2015-11-18 1) Updates to sources and new figures
2015-12-05 1) Renaming ANTEPRIME to PRIME ... consolidating on the pinout for the expansion board.
2016-03-17 1) Releasing new rev for MFG
2016-03-17 1) Synchronizing libraries upon release of multiple products to MFG
2016-04-21 1) Synchronizing some of the reference designators on the BOM vs the schematic (capacitors specifically) 2) Removing the 50pos connector from the BOM -- its supposed to be 64 ... dumbass.
2016-05-01 1) Updating the dissertation as submitted for the prelim
2016-05-05 1) Comments about open collector chip selects
2016-05-09 1) Moved a bunch of test code into appropriate modules. 2) Started porting PEGMA to PRIME
2016-05-12 1) Beginning the port of PEGMA to PRIME
2016-05-20 1) Updating some of the notes regarding power supply voltages on the schematic 2) Updates to the POST procedure for each voltage domain.
2016-05-23 1) Forgot to update the project file
2016-05-24 1) Adding datasheets to the project.
2016-05-31 1) I suppose it would help to commit the new drivers ...
2016-06-01 1) Now I have wifi. Ho Ho Ho.
2016-06-13 1) All peripheral devices now power up and work properly!
2016-07-24 1) Tests are now working through the matlab fixture. However, there appears to be a comms issue thats causing them to get corrupted before plotting (swapping columns, missing a value?)
2016-08-09 1) Deleting some developer specific files and adding the scatter file.
2016-08-09 1) More cleanup
2016-08-26 1) Can now average multiple ADC measurements within getVoltage and getCurrent 2) Linearized a best guess first attempt at the PLR5010D_setCurrent performance is much faster now 3) Added a 'both chann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
2016-08-29 1) Changing the specified sense resistor to metal film from Vishay. The thick film likely has too much inductance and is throwing off measurements.
2016-08-29 1) Revisiting the POST tests to make sure they work (they do) 2) Committing latest changes to the PLR5010D driver -- seems to be more accurate this way... 3) Updates to the current sweep test
2016-09-02 1) Fixing the voltage calculations 2) Updates to the PLR5010 enabling accurate current sinking 3) Fixed the SPI baud rate
2016-09-10 1) Updating the PLR-5010D as-built 2) Adding the linearization xls
2016-09-18 1) Firmware + Software now supports optimal delay testing for HIH, EEPROM and NOR Flash
2016-09-20 1) Initial changes so we can pend on energy.
2016-10-01 1) Had to update the normal amount of energy used in test14
2016-10-03 1) Rearranging plots so that device state is on top!
2016-10-08 1) Consolidating on one MspInit for the LCD. 2) Now turning off the LCD after POST because it interferes with some analog measurements.
2016-10-12 1) PendEnergyTime on the HIH driver 2) Fixing state-monitoring issues with the NOR flash and SDCard 3) PendEnergyTime now works with the 4 channel DMA 5) Configuring the software to work with this ne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
2016-10-16 1) Modifications to support variable timing on SDCards.
2016-10-19 1) SST26 Serial Flash tests now implemented. 2) Working on new format for TED tests -- up to test22 right now.
2016-10-20 1) Updates to iterative testing
2016-10-27 1) This is the final FW and SW used to evaluate PRIME + GPIODVS.
2016-10-28 1) Dumbasses at ST no longer allow for '!' on signals which means that this will now diverge from my schematic ... Geniuses. Changed the ! to _ and migrated the design to the new software version.
2016-10-31 1) Fixing the date time of the result saves 2) Fixing some of the graphs so they dont have 4 sigfigs ticks thus pushing out the labels too far 3) Fixing + saving the animations to gifs 4) Adding devi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
2016-10-31 1) Updating with latest PACER results and fixed the numbering throughout the document.
2016-11-02 1) Dissertation as submitted to the committee pre-defense 2) Working on the defense slides.
2016-11-03 1) Slides post-practice, Updates to PACER coloring
2016-11-10 1) Revised per defense.
2016-11-15 1) Final resubmission to ETD
2017-08-11 1) PACER updates
2017-09-02 1) Adding images
2017-09-21 1) Further review -- changes are tracked
2018-01-04 1) More docs
2018-03-21 1) Committing this because there is a thunder storm...
